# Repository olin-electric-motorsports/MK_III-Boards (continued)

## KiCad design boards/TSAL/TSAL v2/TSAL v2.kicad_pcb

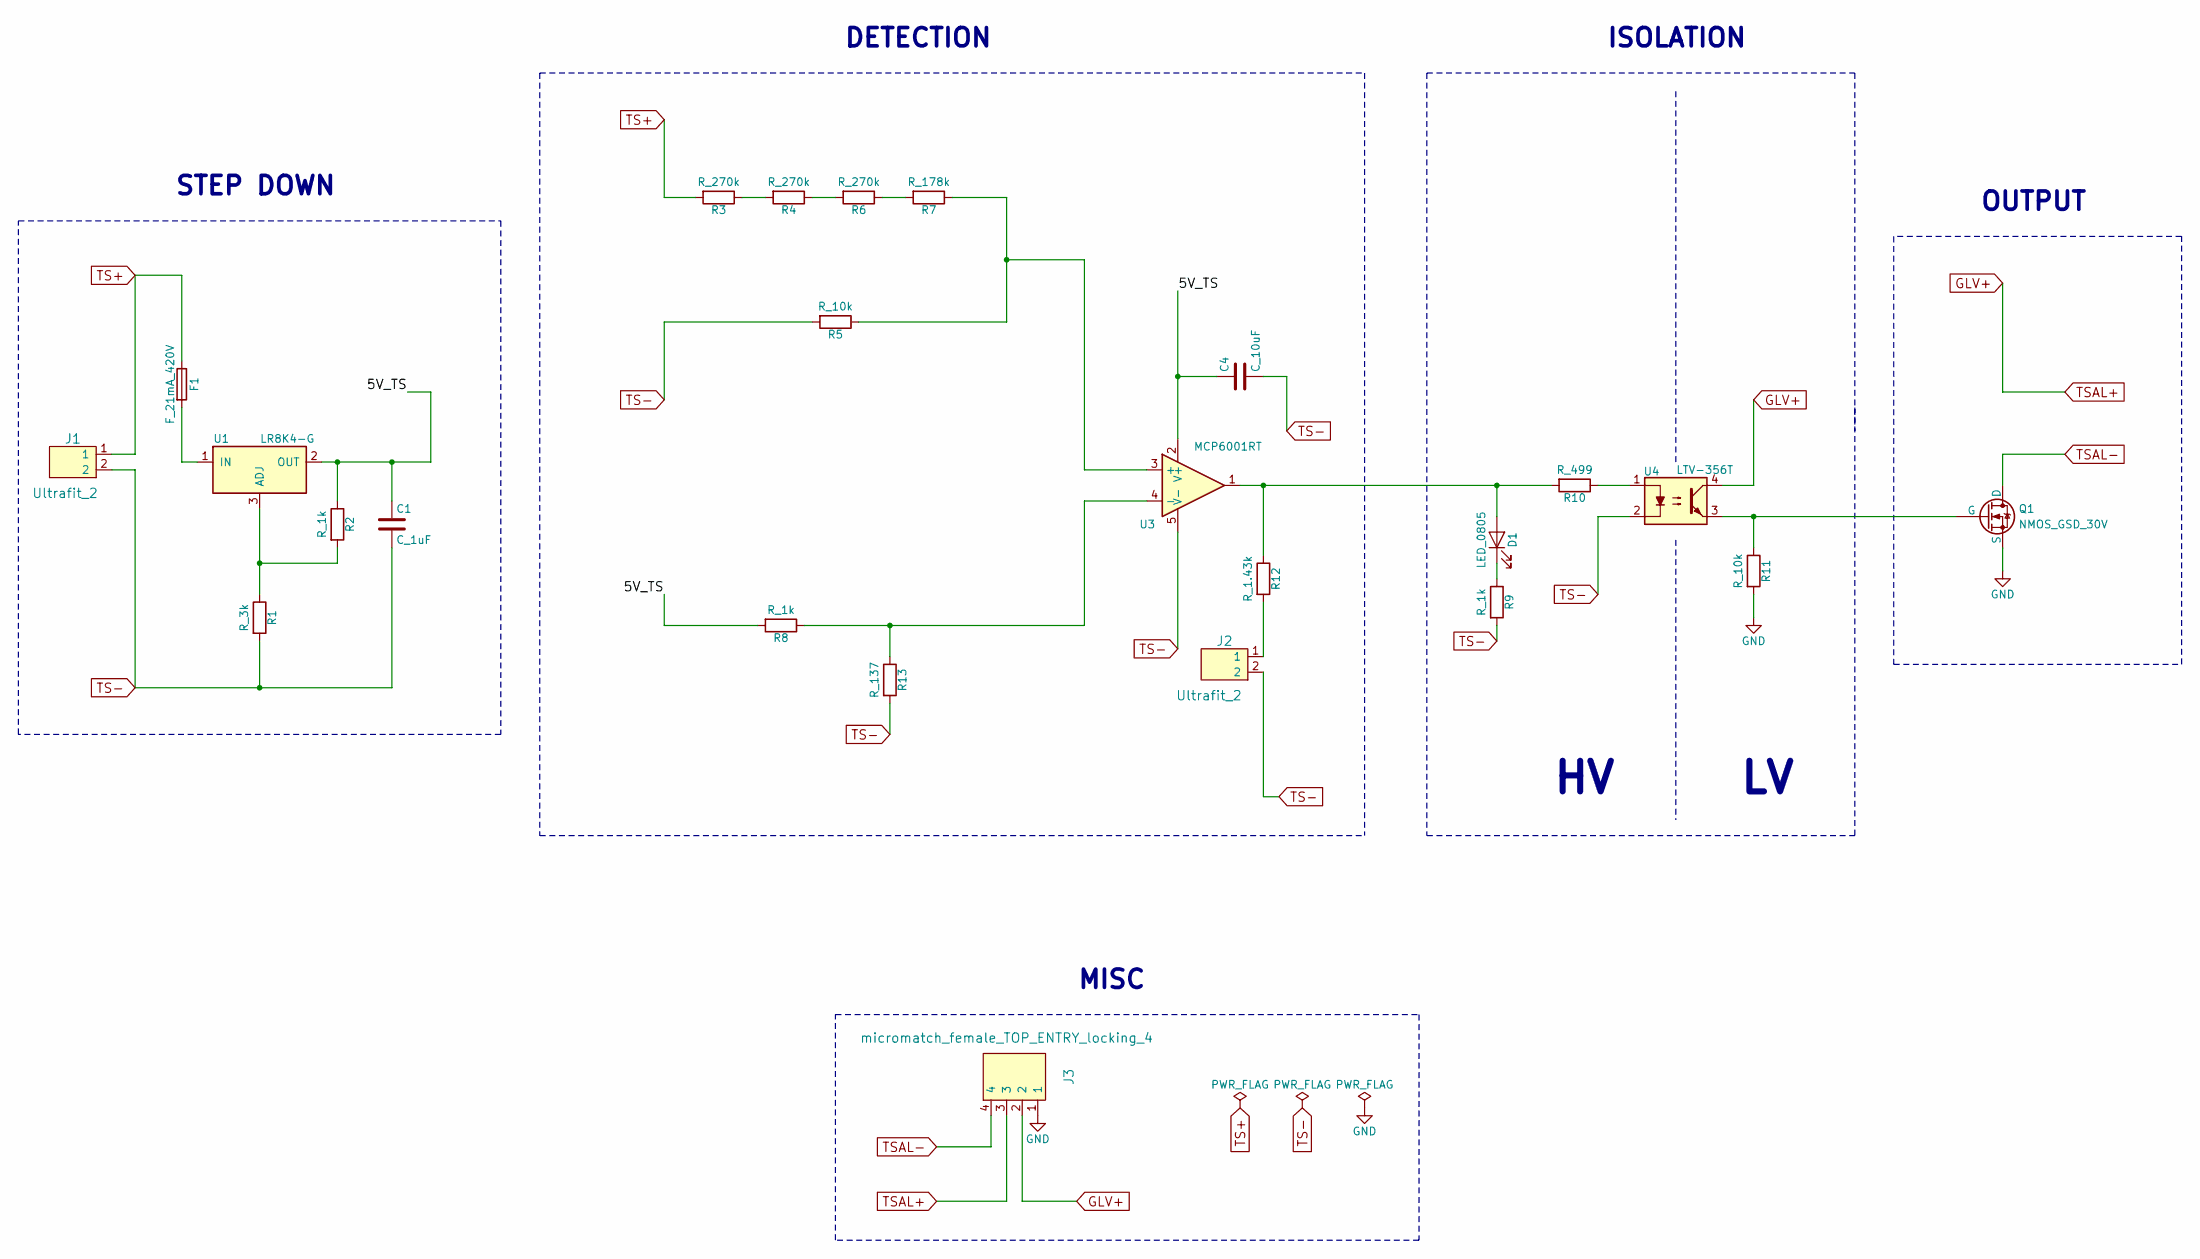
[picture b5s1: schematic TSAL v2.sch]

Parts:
C1: C_1uF; C_0805_OEM; MPN 478-10487-1-ND
C4: C_10uF; C_0805_OEM; MPN 478-5167-1-ND
D1: LED_0805; LED_0805_OEM; MPN 475-1410-1-ND
F1: F_21mA_420V; MPN 495-75309-ND
J1, J2: Ultrafit_2; MPN WM11570-ND
J3: micromatch_female_TOP_ENTRY_locking_4; micromatch_female_vert_4; MPN 338068-4
Q1: NMOS_GSD_30V; SOT-23; MPN SSM3K333RLFCT-ND
R1: R_3k; R_0805_OEM; MPN RMCF0805FT3K00CT-ND
R2, R8, R9: R_1k; R_0805_OEM; MPN RNCP0805FTD1K00CT-ND
R3, R4, R6: R_270k; R_0805_OEM; MPN P270KDACT-ND
R5, R11: R_10k; R_0805_OEM; MPN CRS0805-FX-1002ELFCT-ND
R7: R_178k; R_0805_OEM; MPN P178KDATR-ND
R10: R_499; R_0805_OEM; MPN RC0805FR-07499RL
R12: R_1.43k; R_0805_OEM; MPN A103351CT-ND
R13: R_137; R_0805_OEM; MPN A110460CT-ND
U1: LR8K4-G; TO-252-3_TabPin2; MPN 689-LR8K4-G
U3: MCP6001RT; SOT-23-5_OEM; MPN MCP6001RT-I/OTCT-ND
U4: LTV-356T; SO-4_4.4x3.6mm_Pitch2.54mm

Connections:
/5V_TS: C1.1, C4.1, R2.1, R8.2, U1.2 (OUT), U3.2 (V+)
GLV+: J3.2, J3.3, U4.4
GND: J3.1, Q1.2 (S), R11.2
unnamed: D1.1 (K), R9.1
unnamed: D1.2 (A), R10.2, R12.1, U3.1
unnamed: F1.2, U1.1 (IN)
unnamed: J2.1, R12.2
unnamed: Q1.1 (G), R11.1, U4.3
unnamed: R1.1, R2.2, U1.3 (ADJ)
unnamed: R3.1, R4.2
unnamed: R4.1, R6.2
unnamed: R5.1, R7.1, U3.3 (+)
unnamed: R6.1, R7.2
unnamed: R10.1, U4.1
unnamed: R8.1, R13.1, U3.4 (-)
TS+: F1.1, J1.1, R3.2
TS-: C1.2, C4.2, J1.2, J2.2, R1.2, R5.2, R9.2, R13.2, U3.5 (V-), U4.2
TSAL-: J3.4, Q1.3 (D)

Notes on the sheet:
STEP DOWN
DETECTION
ISOLATION
OUTPUT
MISC

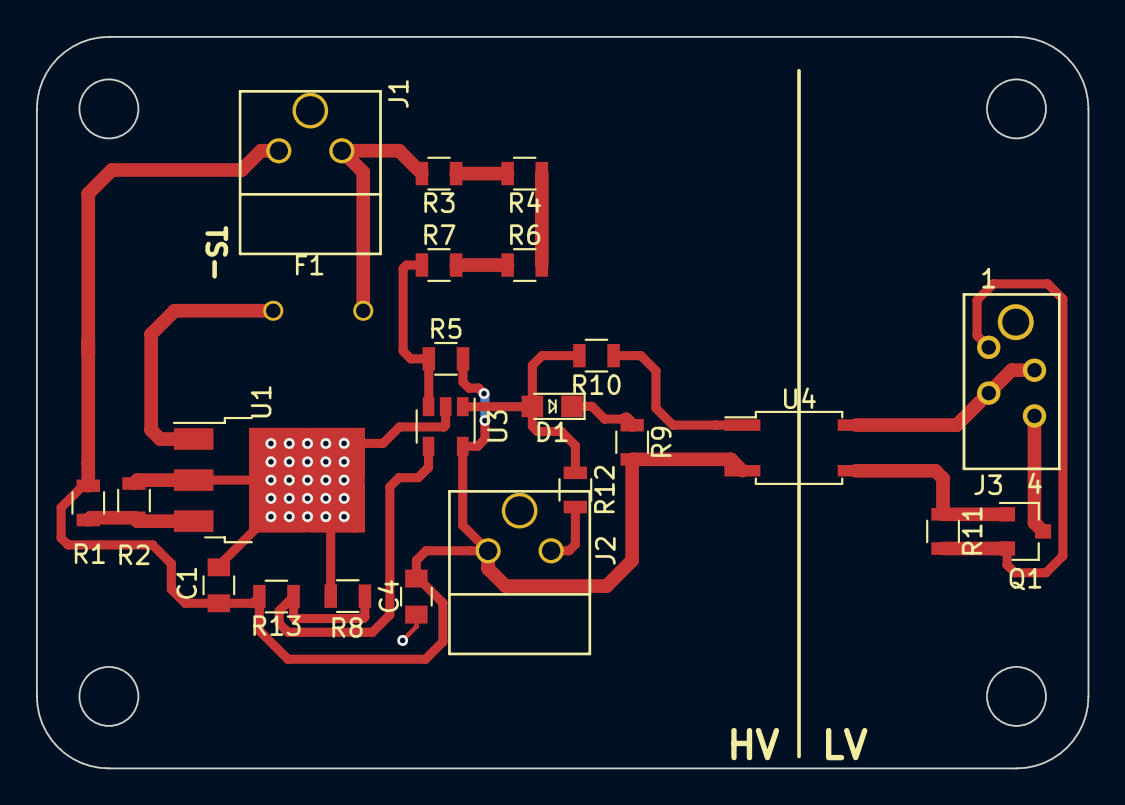
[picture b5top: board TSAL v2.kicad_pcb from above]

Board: 2 copper layers, 58.4 x 40.6 mm, 24 parts (0 on the bottom side), 18 nets.

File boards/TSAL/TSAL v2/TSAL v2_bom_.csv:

Component,Description,Part,References,Value,Footprint,Quantity Per PCB,Datasheet,Package,MPN,MFN,PurchasingLink,Webpage
1,Cap 50V 0.1uF 10% 0805,C_0.1uF,C3,C_0.1uF,C_0805_OEM,1,http://datasheets.avx.com/X7RDielectric.pdf,Value,478-3352-1-ND,Digi-Key,https://www.digikey.com/products/en?keywords=478-3352-1-ND,
2,CAP CER 10UF 10V X5R 0805,C_10uF,C4,C_10uF,C_0805_OEM,1,http://datasheets.avx.com/cx5r.pdf,Value,478-5167-1-ND,Digi-Key,https://www.digikey.com/product-detail/en/avx-corporation/08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,
3,CAP CER 1UF 25V X7R 0805,C_1uF,C1 C2,C_1uF,C_0805_OEM,2,http://datasheets.avx.com/X7RDielectric.pdf,Value,478-10487-1-ND,Digi-Key,https://www.digikey.com/product-detail/en/avx-corporation/08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,
4,LED_0805,LED_0805,D1,LED_0805,LED_0805_OEM,1,http://www.osram-os.com/Graphics/XPic9/00078860_0.pdf,Value,475-1410-1-ND,Digi-Key,https://www.digikey.com/products/en?keywords=475-1410-1-ND,
5,PTC Fuse 420V 21mA,F_21mA_420V,F1,F_21mA_420V,F_21mA_420V,1,https://en.tdk.eu/inf/55/db/PTC/PTC_OC_Leaded_380V_500V.pdf,,495-75309-ND,Digi-Key,https://www.digikey.com/product-detail/en/epcos-tdk/B59884C0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,
6,ULTRAFIT CONN HDR 02CKT,Ultrafit_2,J1 J2,Ultrafit_2,Ultrafit_2,2,,Value,WM11570-ND,Digi-Key,https://www.digikey.com/product-detail/en/molex-llc/17228611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,
7,CONN FMALE-ON-BRD 4POS VERT T/H,micromatch_female_TOP_ENTRY_locking_4,J3,micromatch_female_TOP_ENTRY_locking_4,micromatch_female_vert_4,1,http://www.te.com/commerce/DocumentDelivery/DDEController?Ac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,Value,338068-4,Digi-Key,https://www.digikey.com/product-detail/en/te-connectivity-am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,
8,N-channel MOSFET,NMOS_GSD_30V,Q1,NMOS_GSD_30V,SOT-23,1,https://www.digikey.com/products/en?keywords=SSM3K333RLFCT-ND,Value,SSM3K333RLFCT-ND,Digi-Key,https://www.digikey.com/products/en?keywords=SSM3K333RLFCT-ND,
9,RES SMD 1.43KOHM 0.1% 1/10W 0805,R_1.43k,R12,R_1.43k,R_0805_OEM,1,https://media.digikey.com/pdf/Data%20Sheets/Tyco%20Electonic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,,A103351CT-ND,Digi-Key,https://www.digikey.com/product-detail/en/te-connectivity-pa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,
10,Res 10k 1%,R_10k,R5 R11,R_10k,R_0805_OEM,2,http://www.bourns.com/data/global/pdfs/CRS.pdf,Value,CRS0805-FX-1002ELFCT-ND,Digi-Key,https://www.digikey.com/products/en?keywords=CRS0805-FX-1002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,
11,RES SMD 178K OHM 0.1% 1/8W 0805,R_178k,R7,R_178k,R_0805_OEM,1,https://industrial.panasonic.com/cdbs/www-data/pdf/RDM0000/A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,,P178KDATR-ND,Digikey,,https://www.digikey.com/product-detail/en/panasonic-electron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
12,Res 1k 1%,R_1k,R2 R8 R9,R_1k,R_0805_OEM,3,https://www.seielect.com/Catalog/SEI-rncp.pdf,Value,RNCP0805FTD1K00CT-ND,Digi-Key,https://www.digikey.com/products/en?keywords=RNCP0805FTD1K00CT-ND,
13,RES SMD 270K OHM 0.1% 1/8W 0805,R_270k,R3 R4 R6,R_270k,R_0805_OEM,3,https://industrial.panasonic.com/cdbs/www-data/pdf/RDM0000/A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,,P270KDACT-ND,DigiKey,,https://www.digikey.com/product-detail/en/panasonic-electron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
14,Res 3k 1% 0805 1/8W,R_3k,R1,R_3k,R_0805_OEM,1,https://www.seielect.com/Catalog/SEI-RMCF_RMCP.pdf,Value,RMCF0805FT3K00CT-ND,Digi-Key,https://www.digikey.com/product-detail/en/stackpole-electron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,
15,Res 499 1%,R_499,R10,R_499,R_0805_OEM,1,http://www.yageo.com.tw/exep/pages/download/literatures/PYu-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,Value,RC0805FR-07499RL,Digi-Key,https://www.digikey.com/product-detail/en/yageo/RC0805FR-074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,
16,Linear Voltage Regulators 450V Adj 3 Termnl,LR8K4-G,U1,LR8K4-G,TO-252-3_TabPin2,1,http://ww1.microchip.com/downloads/en/DeviceDoc/20005399B.pdf,,689-LR8K4-G,Mouser,,https://www.mouser.com/productdetail/?qs=jWmFlM7coATgElKtQd9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
17,"DC Optocoupler, Vce 80V, CTR 50%, SO-4",LTV-356T,U4,LTV-356T,SO-4_4.4x3.6mm_Pitch2.54mm,1,http://optoelectronics.liteon.com/upload/download/DS70-2001-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,,,,,
18,IC OPAMP GP 1MHZ RRO SOT23-5  1.8-6V,MCP6001RT,U3,MCP6001RT,SOT-23-5_OEM,1,http://ww1.microchip.com/downloads/en/DeviceDoc/21733j.pdf,Value,MCP6001RT-I/OTCT-ND,Digi-Key,https://www.digikey.com/product-detail/en/microchip-technolo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,
19,IC VREF SHUNT ADJ SOT353,ZXRE160,U2,ZXRE160,ZXRE160,1,https://www.diodes.com/assets/Datasheets/ZXRE160.pdf,,ZXRE160FT4-7DICT-ND,DigiKey,,https://www.digikey.com/product-detail/en/diodes-incorporate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





Component Groups:,19
Component Count:,26
Fitted Components:,26
Number of PCBs:,1
Total components:,26
Schematic Version:,
Schematic Date:,
BoM Date:,2/7/2018 4:59:53 PM
Schematic Source:,C:\Users\ugupta\Documents\GitHub\MK_III-Boards\boards\TSAL\TSAL v2\TSAL v2.sch
KiCad Version:,Eeschema 4.0.7

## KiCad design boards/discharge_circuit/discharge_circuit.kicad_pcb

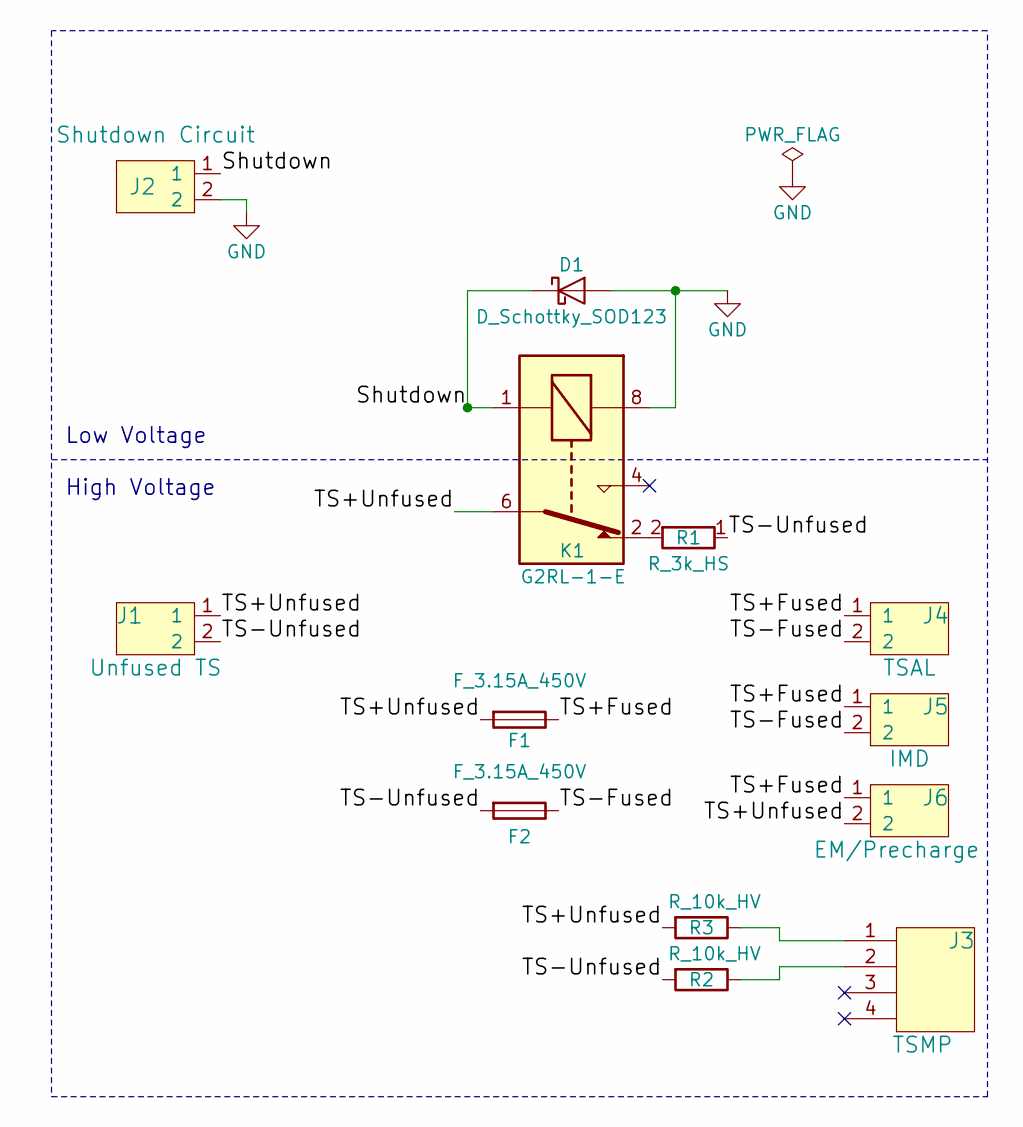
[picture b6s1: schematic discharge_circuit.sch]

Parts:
D1: D_Schottky_SOD123; D_SOD-123W_OEM; MPN 1727-2394-1-ND
F1, F2: F_3.15A_450V; Fuse_TE7_Littelfuse-807Series; MPN 80713150440
J1: Unfused TS; Ultrafit_2; MPN WM11570-ND
J2: Shutdown Circuit; Ultrafit_2; MPN WM11570-ND
J3: TSMP; mx150l_2
J4: TSAL; Ultrafit_2; MPN WM11570-ND
J5: IMD; Ultrafit_2; MPN WM11570-ND
J6: EM/Precharge; Ultrafit_2; MPN WM11570-ND
K1: G2RL-1-E; Relay_SPDT_OMRON-G2RL-1-E; MPN Z2834-ND
R1: R_3k_HS; R_3k_HS_TO247; MPN AP101 3K J
R2, R3: R_10k_HV; R_10K_HV; MPN PPC5D10.0KCT-ND

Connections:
/Shutdown: D1.1 (K), J2.1, K1.1
/TS+Fused: F1.1, J4.1, J5.1, J6.1
/TS+Unfused: F1.2, J1.1, J6.2, K1.6, R3.2
/TS-Fused: F2.1, J4.2, J5.2
/TS-Unfused: F2.2, J1.2, R1.1, R2.2
GND: D1.2 (A), J2.2, K1.8
unnamed: J3.1, R3.1
unnamed: J3.2, R2.1
unnamed: K1.2, R1.2

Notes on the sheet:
High Voltage
Low Voltage

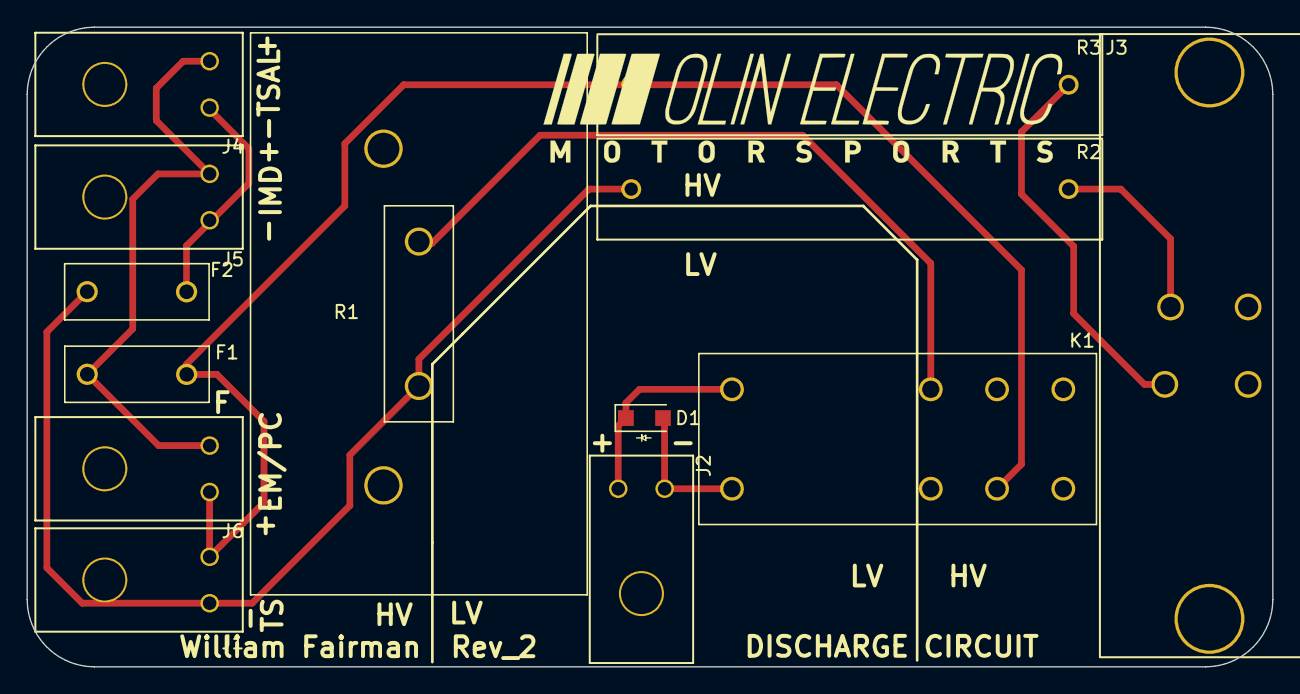
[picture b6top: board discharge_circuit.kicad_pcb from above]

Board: 2 copper layers, 94.0 x 48.3 mm, 13 parts (0 on the bottom side), 9 nets.

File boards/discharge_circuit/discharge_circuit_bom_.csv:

Component,Description,Part,References,Value,Footprint,Quantity Per PCB,Datasheet,MPN,MFN,PurchasingLink,Package
1,DIODE SCHOTTKY 100V 1A SOD123,D_Schottky_SOD123,D1,D_Schottky_SOD123,D_SOD-123W_OEM,1,https://assets.nexperia.com/documents/data-sheet/PMEG10010ELR.pdf,1727-2394-1-ND,Digi-Key,https://www.digikey.com/product-detail/en/nexperia-usa-inc/P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,
2,,F_3.15A_450V,F1 F2,F_3.15A_450V,Fuse_TE7_Littelfuse-807Series,2,http://www.mouser.com/ds/2/240/Littelfuse_Fuse_807_Datasheet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,80713150440,Mouser,https://www.mouser.com/ProductDetail/Littelfuse/80713150440/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,Value
3,ULTRAFIT CONN HDR 02CKT,Ultrafit_2,J6,EM/Precharge,Ultrafit_2,1,,WM11570-ND,Digi-Key,https://www.digikey.com/product-detail/en/molex-llc/17228611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,Value
4,ULTRAFIT CONN HDR 02CKT,Ultrafit_2,J5,IMD,Ultrafit_2,1,,WM11570-ND,Digi-Key,https://www.digikey.com/product-detail/en/molex-llc/17228611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,Value
5,ULTRAFIT CONN HDR 02CKT,Ultrafit_2,J2,Shutdown Circuit,Ultrafit_2,1,,WM11570-ND,Digi-Key,https://www.digikey.com/product-detail/en/molex-llc/17228611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,Value
6,ULTRAFIT CONN HDR 02CKT,Ultrafit_2,J4,TSAL,Ultrafit_2,1,,WM11570-ND,Digi-Key,https://www.digikey.com/product-detail/en/molex-llc/17228611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,Value
7,mx150L_2,mx150L_2,J3,TSMP,mx150l_2,1,http://www.literature.molex.com/SQLImages/kelmscott/Molex/PD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,,,,Value
8,ULTRAFIT CONN HDR 02CKT,Ultrafit_2,J1,Unfused TS,Ultrafit_2,1,,WM11570-ND,Digi-Key,https://www.digikey.com/product-detail/en/molex-llc/17228611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,Value
9,"Omron G5G relay, Miniature Single Pole, SPDT, 10A",G2RL-1-E,K1,G2RL-1-E,Relay_SPDT_OMRON-G2RL-1-E,1,http://omronfs.omron.com/en_US/ecb/products/pdf/en-g2rl.pdf,Z2834-ND,Digi-Key,https://www.digikey.com/product-detail/en/omron-electronics-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,Value
10,Res 10k 1%,R_10k_HV,R2 R3,R_10k_HV,R_10K_HV,2,http://www.vishay.com/docs/28731/pacserie.pdf,PPC5D10.0KCT-ND,Digi-Key,https://www.digikey.com/products/en?keywords=PPC5D10.0KCT-ND,Value
11,3k ohm 100 w rating,R_3k_HS,R1,R_3k_HS,R_3k_HS_TO247,1,http://dpk3n3gg92jwt.cloudfront.net/domains/ohmite/pdf/acl_a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,AP101 3K J,Digi-Key,https://www.digikey.com/product-detail/en/ohmite/AP101-3K-J/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,Value





Component Groups:,11
Component Count:,13
Fitted Components:,13
Number of PCBs:,1
Total components:,13
Schematic Version:,
Schematic Date:,
BoM Date:,Mon 05 Feb 2018 09:41:58 PM EST
Schematic Source:,/home/william/Desktop/Formula/MK_III-Boards/boards/discharge_circuit/discharge_circuit.sch
KiCad Version:,Eeschema 4.0.7-e2-6376~58~ubuntu16.04.1

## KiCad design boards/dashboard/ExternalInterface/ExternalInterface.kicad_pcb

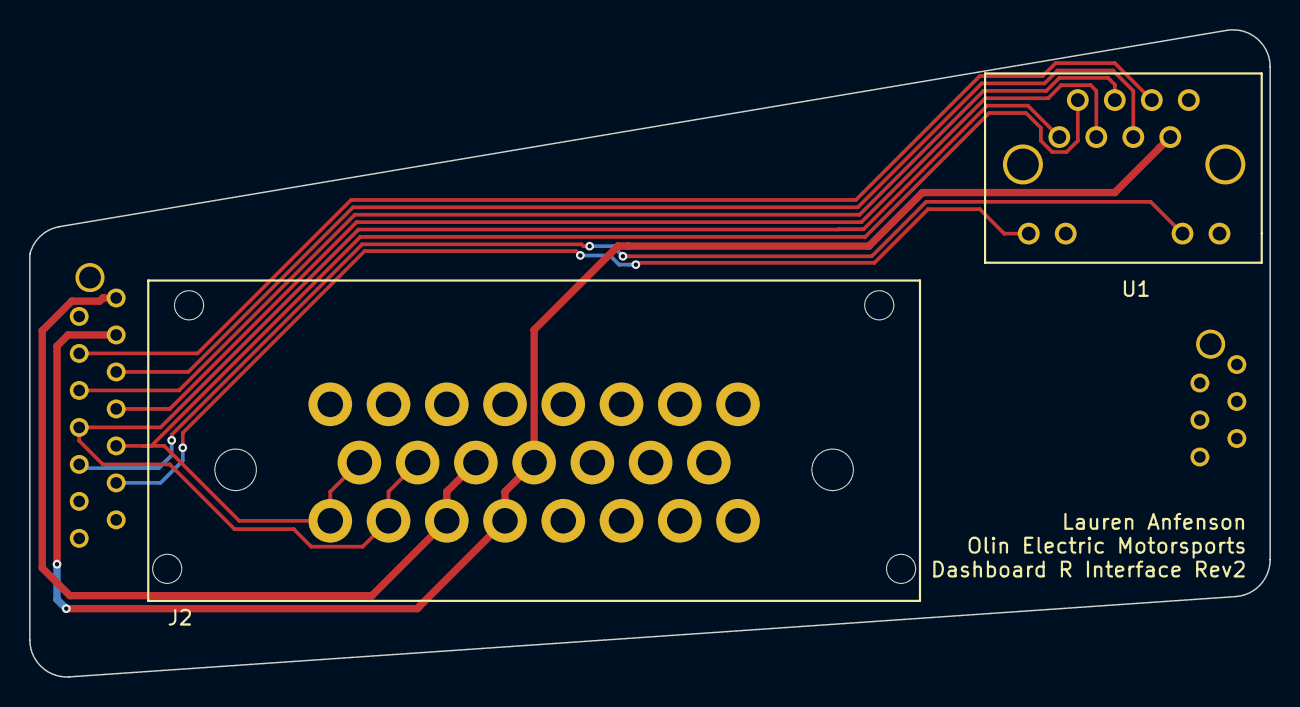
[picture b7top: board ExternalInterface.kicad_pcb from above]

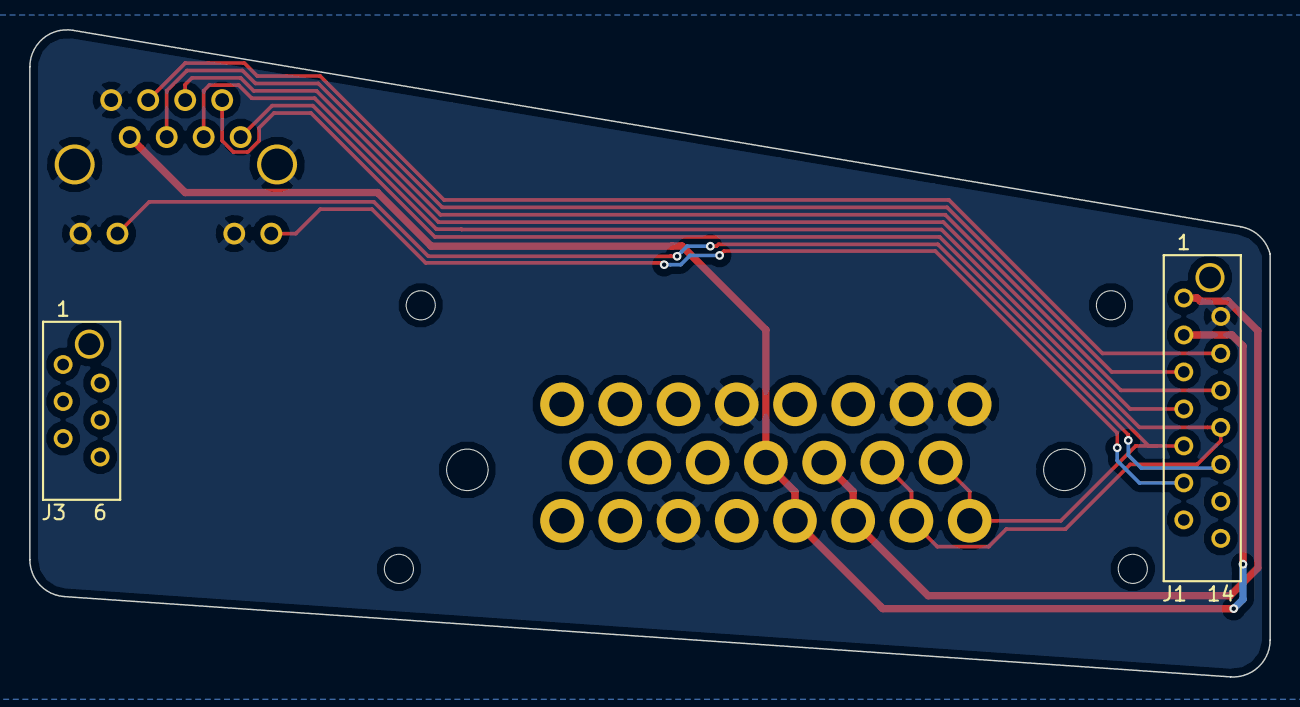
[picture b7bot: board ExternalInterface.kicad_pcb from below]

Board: 2 copper layers, 85.2 x 44.4 mm, 4 parts (2 on the bottom side), 11 nets.

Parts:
J1: micromatch_female_TOP_ENTRY_locking_14; micromatch_female_vert_14
J2: Ampseal_23
J3: micromatch_female_TOP_ENTRY_locking_6; micromatch_female_vert_6
U1: RJ45_VT; RJ45-Vertical

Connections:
+12V: J1.1, J2.11, J2.18
AT_RESET: J1.7, U1.3
CANH: J1.9, J2.9, J2.16, U1.2
CANL: J1.8, J2.10, J2.17, U1.1
GND: J1.2, J2.1, J2.2, J2.5, J2.21, U1.8, U1.9, U1.11, U1.13, U1.14
LED1: J1.10, U1.10
LED2: J1.11, U1.12
MISO: J1.5, U1.5
MOSI: J1.4, U1.6
SCK: J1.6, U1.4
VCC: J1.3, J2.12, J2.19, U1.7

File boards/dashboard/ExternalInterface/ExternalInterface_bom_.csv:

Component,Description,Part,References,Value,Footprint,Quantity Per PCB,Datasheet,Package,MPN,MFN,PurchasingLink
1,Waterproof Panel-Mount Connector RA 14-Pin,Ampseal_14,J2,Ampseal_14,Ampseal_14,1,,,,,
2,CONN FMALE-ON-BRD 14POS VERT T/H,micromatch_female_TOP_ENTRY_locking_14,J1,micromatch_female_TOP_ENTRY_locking_14,micromatch_female_vert_14,1,,Value,A99502CT-ND,Digi-Key,https://www.digikey.com/product-detail/en/te-connectivity-am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
3,CONN FMALE-ON-BRD 6POS VERT T/H,micromatch_female_TOP_ENTRY_locking_6,J3,micromatch_female_TOP_ENTRY_locking_6,micromatch_female_vert_6,1,,Value,A99437CT-ND,Digi-Key,https://www.digikey.com/product-detail/en/te-connectivity-am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
4,,RJ45_VT,U1,RJ45_VT,RJ45-Vertical,1,,,,,





Component Groups:,4
Component Count:,4
Fitted Components:,4
Number of PCBs:,1
Total components:,4
Schematic Version:,
Schematic Date:,
BoM Date:,Wed 21 Feb 2018 10:11:25 PM EST
Schematic Source:,/home/lanfenson/MK_III-Boards-master/boards/dashboard/ExternalInterface/ExternalInterface.sch
KiCad Version:,Eeschema 4.0.7-e2-6376~58~ubuntu16.04.1

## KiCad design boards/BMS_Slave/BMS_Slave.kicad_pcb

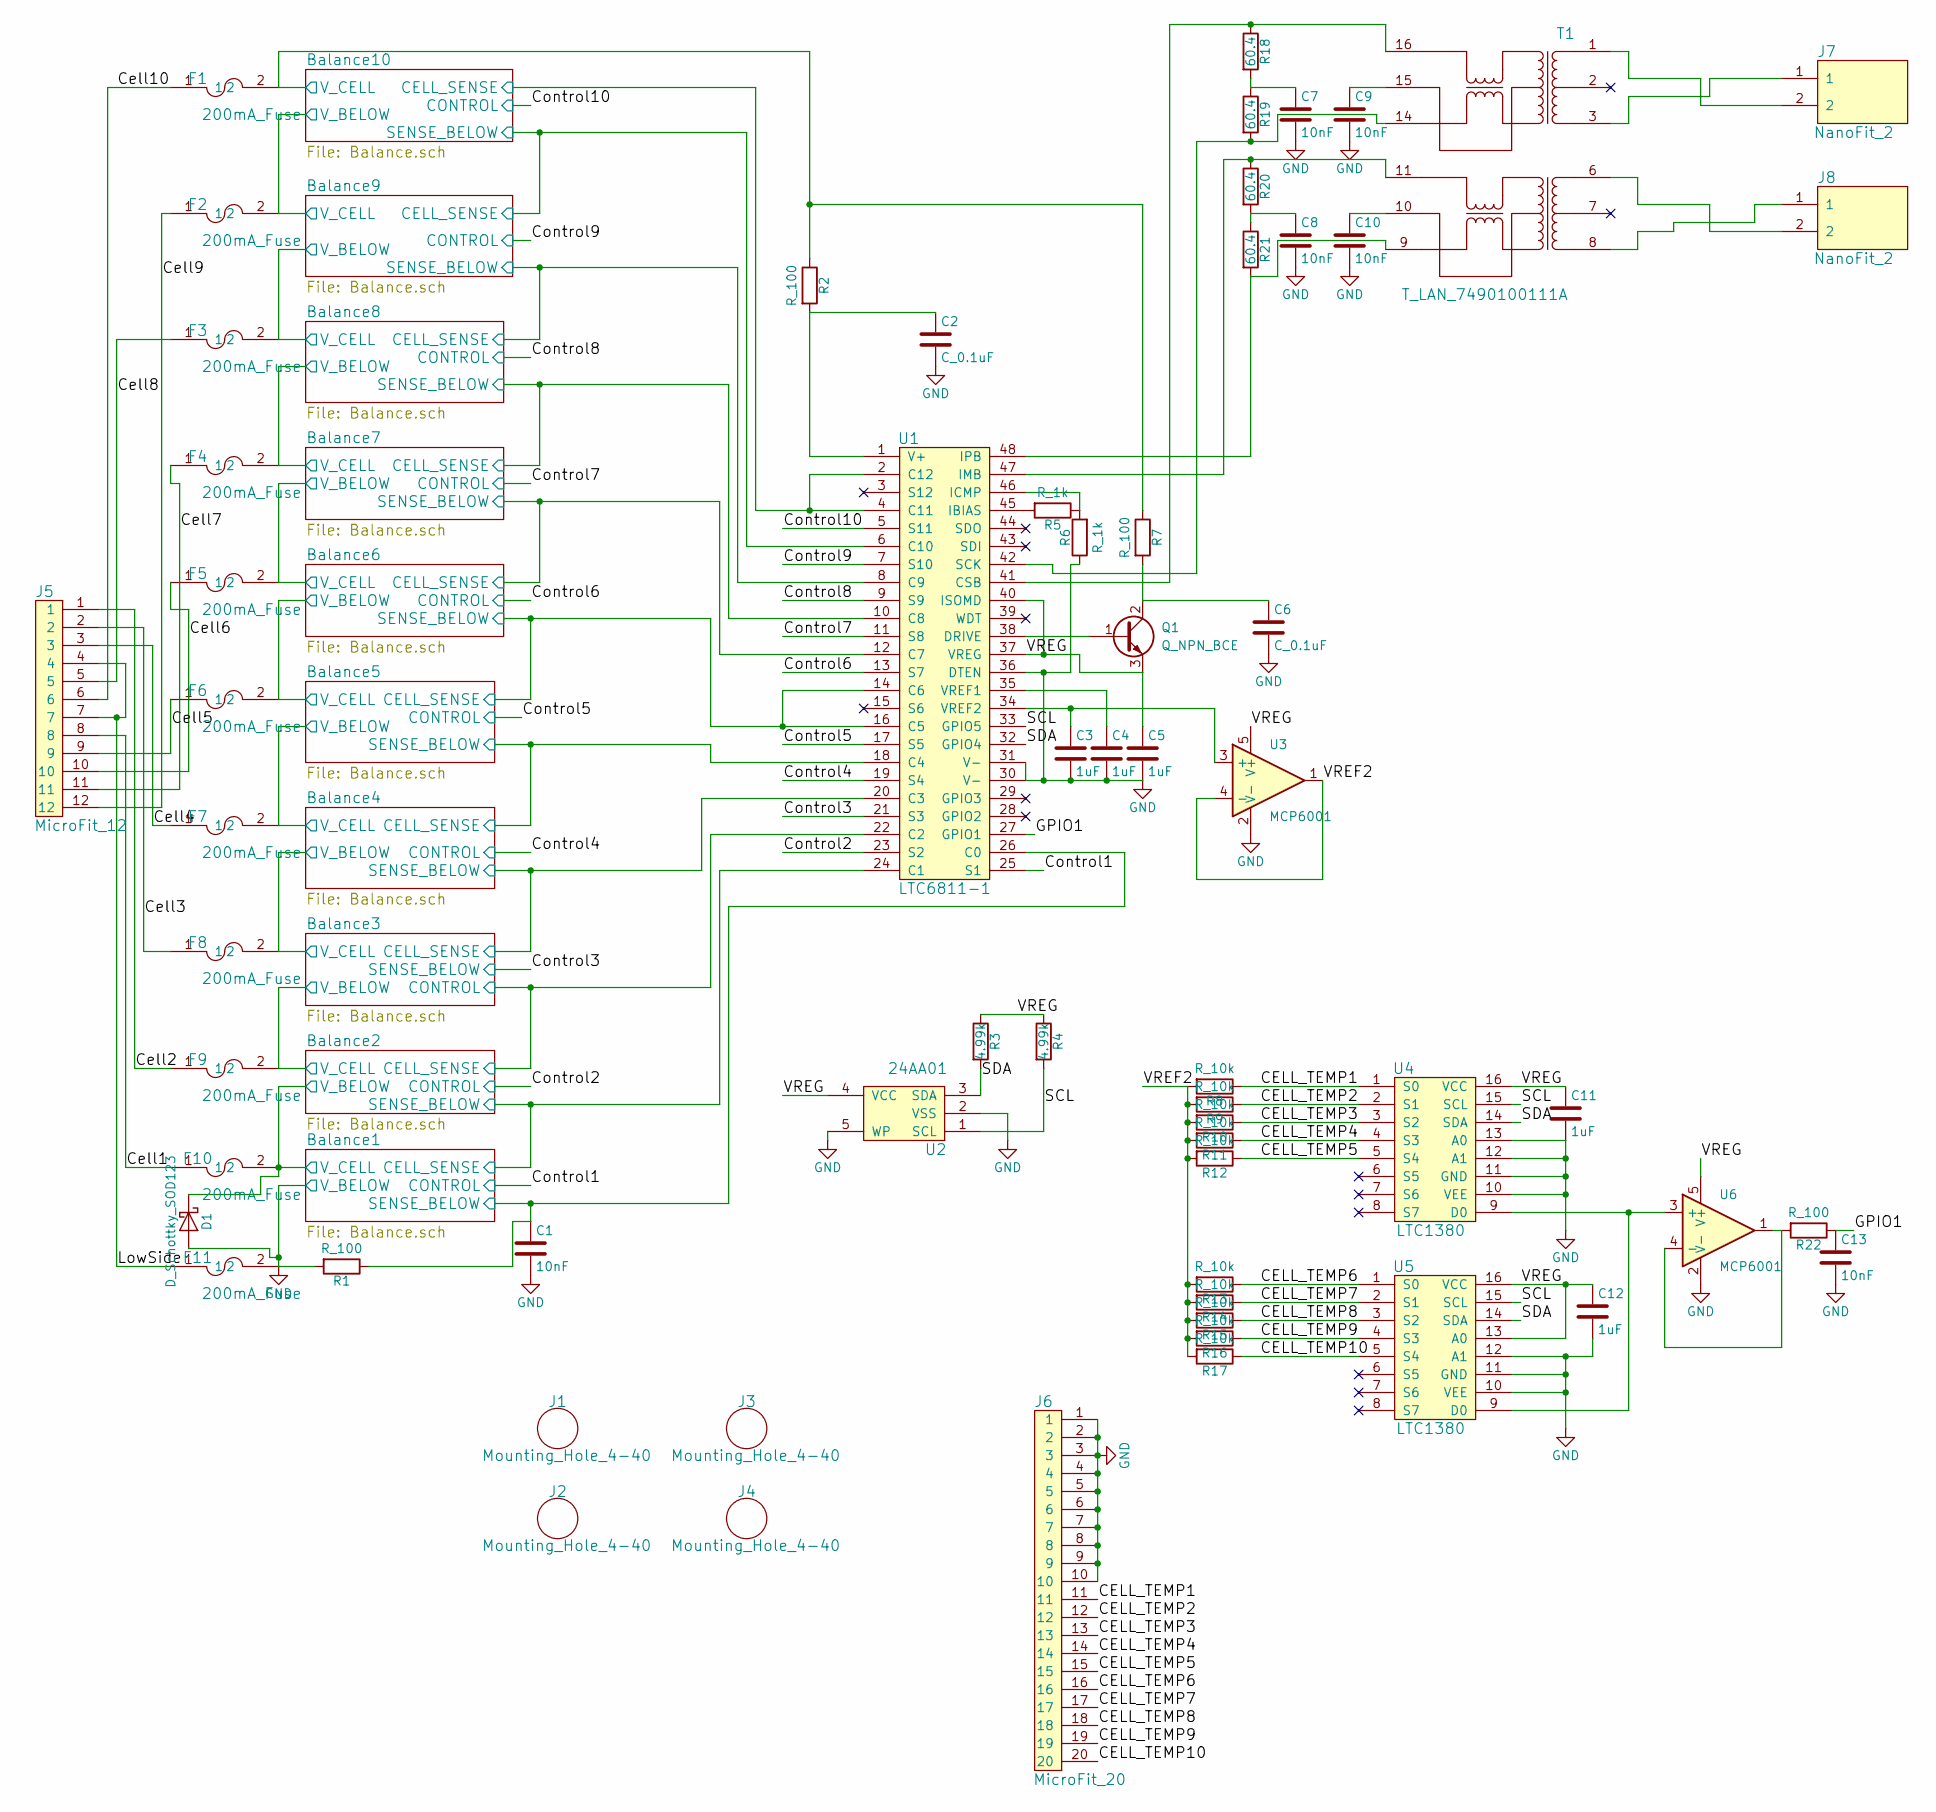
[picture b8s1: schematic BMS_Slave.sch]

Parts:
C1, C7, C8, C9, C10, C13: 10nF; C_0805_OEM
C2, C6: C_0.1uF; C_0805_OEM; MPN 478-3352-1-ND
C3, C4, C5, C11, C12: 1uF; C_0805_OEM
D1: D_Schottky_SOD123; D_SOD-123W_OEM; MPN 1727-2394-1-ND
F1, F2, F3, F4, F5, F6, F7, F8, F9, F10, F11: 200mA_Fuse; Fuse_1812
J1, J3: Mounting_Hole_4-40; MPN Value
J2, J4: Mounting_Hole_4-40; Mounting_Hole_Insert_4-40; MPN Value
J5: MicroFit_12; Microfit3_Header_02x06_Angled_OEM
J6: MicroFit_20; Molex_Microfit3_Header_02x10_Angled_OEM
J7, J8: NanoFit_2; Molex_NanoFit_1x02x2.50mm_Angled_OEM
Q1: Q_NPN_BCE; SOT-223
R1, R2, R7, R22: R_100; R_0805_OEM; MPN RNCP0805FTD100RCT-ND
R3, R4: 4.99k; R_0805_OEM
R5, R6: R_1k; R_0805_OEM; MPN RNCP0805FTD1K00CT-ND
R8, R9, R10, R11, R12, R13, R14, R15, R16, R17: R_10k; R_0805_OEM; MPN CRS0805-FX-1002ELFCT-ND
R18, R19, R20, R21: 60.4; R_0805_OEM
T1: T_LAN_7490100111A; 7490100111A
U1: LTC6811-1; TSSOP-48_LTC6811-1
U2: 24AA01; SOT-23-5_OEM
U3, U6: MCP6001; SOT-23-5_OEM
U4, U5: LTC1380; SSOP-16_LTC1380

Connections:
/Balance1/CELL_SENSE: U1.24 (C1); also elsewhere on the board
/Balance1/SENSE_BELOW: C1.1, R1.1, U1.26 (C0); also elsewhere on the board
/Balance2/CELL_SENSE: U1.22 (C2); also elsewhere on the board
/Balance2/V_BELOW: D1.1 (K), F10.2; also elsewhere on the board
/Balance3/CELL_SENSE: U1.20 (C3); also elsewhere on the board
/Balance3/V_BELOW: F9.2; also elsewhere on the board
/Balance4/CELL_SENSE: U1.18 (C4); also elsewhere on the board
/Balance4/V_BELOW: F8.2; also elsewhere on the board
/Balance5/CELL_SENSE: U1.14 (C6), U1.16 (C5); also elsewhere on the board
/Balance5/V_BELOW: F7.2; also elsewhere on the board
/Balance6/CELL_SENSE: U1.12 (C7); also elsewhere on the board
/Balance6/V_BELOW: F6.2; also elsewhere on the board
/Balance7/CELL_SENSE: U1.10 (C8); also elsewhere on the board
/Balance8/CELL_SENSE: U1.8 (C9); also elsewhere on the board
/Balance8/V_BELOW: F4.2; also elsewhere on the board
/Balance9/CELL_SENSE: U1.6 (C10); also elsewhere on the board
/Balance10/CELL_SENSE: U1.2 (C12), U1.4 (C11); also elsewhere on the board
/Balance10/V_BELOW: F2.2; also elsewhere on the board
/Balance10/V_CELL: F1.2, R2.1, R7.1; also elsewhere on the board
/CELL_TEMP1: J6.11, R8.1, U4.1 (S0)
/CELL_TEMP2: J6.12, R9.1, U4.2 (S1)
/CELL_TEMP3: J6.13, R10.1, U4.3 (S2)
/CELL_TEMP4: J6.14, R11.1, U4.4 (S3)
/CELL_TEMP5: J6.15, R12.1, U4.5 (S4)
/CELL_TEMP6: J6.16, R13.1, U5.1 (S0)
/CELL_TEMP7: J6.17, R14.1, U5.2 (S1)
/CELL_TEMP8: J6.18, R15.1, U5.3 (S2)
/CELL_TEMP9: J6.19, R16.1, U5.4 (S3)
/CELL_TEMP10: J6.20, R17.1, U5.5 (S4)
/Cell1: F10.1, J5.8
/Cell2: F9.1, J5.1
/Cell3: F8.1, J5.2
/Cell4: F7.1, J5.3
/Cell5: F6.1, J5.9
/Cell6: F5.1, J5.10
/Cell7: F4.1, J5.11
/Cell8: F3.1, J5.5
/Cell9: F2.1, J5.12
/Cell10: F1.1, J5.6
/Control1: U1.25 (S1); also elsewhere on the board
/Control2: U1.23 (S2); also elsewhere on the board
/Control3: U1.21 (S3); also elsewhere on the board
/Control4: U1.19 (S4); also elsewhere on the board
/Control5: U1.17 (S5); also elsewhere on the board
/Control6: U1.13 (S7); also elsewhere on the board
/Control7: U1.11 (S8); also elsewhere on the board
/Control8: U1.9 (S9); also elsewhere on the board
/Control9: U1.7 (S10); also elsewhere on the board
/Control10: U1.5 (S11); also elsewhere on the board
/GPIO1: C13.1, R22.1, U1.27 (GPIO1)
/LowSide: F11.1, J5.4, J5.7
/SCL: R4.2, U1.33 (GPIO5), U2.1 (SCL), U4.15 (SCL), U5.15 (SCL)
/SDA: R3.2, U1.32 (GPIO4), U2.3 (SDA), U4.14 (SDA), U5.14 (SDA)
/VREF2: R8.2, R9.2, R10.2, R11.2, R12.2, R13.2, R14.2, R15.2, R16.2, R17.2, U3.1, U3.4 (-)
/VREG: C5.1, C11.1, C12.1, Q1.3 (E), R3.1, R4.1, U1.37 (VREG), U1.40 (ISOMD), U2.4 (VCC), U3.5 (V+), U4.16 (VCC), U5.13 (A0), U5.16 (VCC), U6.5 (V+)
GND: C1.2, C2.2, C3.2, C4.2, C5.2, C6.2, C7.2, C8.2, C9.2, C10.2, C11.2, C12.2, C13.2, D1.2 (A), F11.2, J6.1, J6.2, J6.3, J6.4, J6.5, J6.6, J6.7, J6.8, J6.9, J6.10, R1.2, R6.1, U1.30 (V-), U1.31 (V-), U1.36 (DTEN), U2.2 (VSS), U2.5 (WP), U3.2 (V-), U4.10 (VEE), U4.11 (GND), U4.12 (A1), U4.13 (A0), U5.10 (VEE), U5.11 (GND), U5.12 (A1), U6.2 (V-); also elsewhere on the board
unnamed: C2.1, R2.2, U1.1 (V+)
unnamed: C3.1, U1.34 (VREF2), U3.3 (+)
unnamed: C4.1, U1.35 (VREF1)
unnamed: C6.1, Q1.2 (C), R7.2
unnamed: C7.1, R18.2, R19.1
unnamed: C8.1, R20.2, R21.1
unnamed: C9.1, T1.15
unnamed: C10.1, T1.10
unnamed: J7.1, T1.3
unnamed: J7.2, T1.1
unnamed: J8.1, T1.8
unnamed: J8.2, T1.6
unnamed: Q1.1 (B), U1.38 (DRIVE)
unnamed: R5.1, R6.2, U1.46 (ICMP)
unnamed: R5.2, U1.45 (IBIAS)
unnamed: R18.1, T1.16, U1.41 (CSB)
unnamed: R19.2, T1.14, U1.42 (SCK)
unnamed: R20.1, T1.11, U1.47 (IMB)
unnamed: R21.2, T1.9, U1.48 (IPB)
unnamed: R22.2, U6.1, U6.4 (-)
unnamed: U4.9 (D0), U5.9 (D0), U6.3 (+)

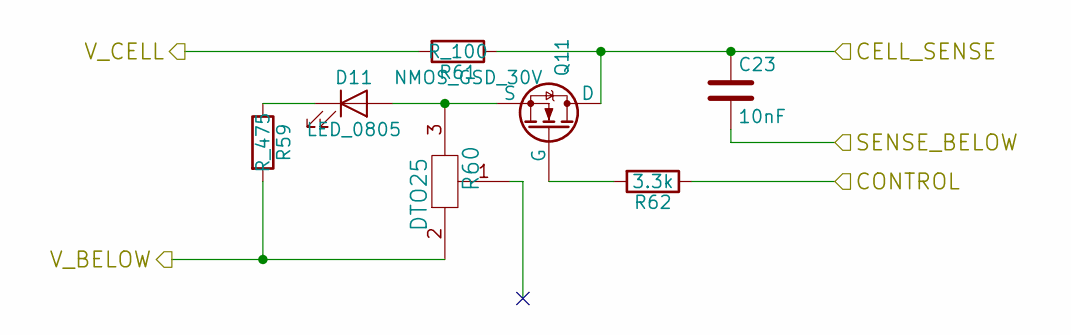
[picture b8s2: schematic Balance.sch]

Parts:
C14: 10nF; C_0805_OEM
D2: LED_0805; LED_0805_OEM; MPN 475-1410-1-ND
Q2: NMOS_GSD_30V; SOT-23F; MPN SSM3K333RLFCT-ND
R23: R_475; R_0805_OEM; MPN 311-475CRCT-ND
R25: R_100; R_0805_OEM; MPN RNCP0805FTD100RCT-ND
R26: 3.3k; R_0805_OEM
R32: DTO25

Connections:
/Balance8/CELL_SENSE: C14.2; also elsewhere on the board
/Balance9/CELL_SENSE: C14.1, Q2.3 (D), R25.1; also elsewhere on the board
/Balance10/V_BELOW: R25.2; also elsewhere on the board
/Control9: R26.1; also elsewhere on the board
unnamed: D2.1 (K), R23.1
unnamed: Q2.1 (G), R26.2

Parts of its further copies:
C15, C16, C17, C18, C19, C20, C21, C22, C23: 10nF; C_0805_OEM
D3, D4, D5, D6, D7, D8, D9, D10, D11: LED_0805; LED_0805_OEM; MPN 475-1410-1-ND
Q3, Q4, Q5, Q6, Q7, Q8, Q9, Q10, Q11: NMOS_GSD_30V; SOT-23F; MPN SSM3K333RLFCT-ND
R24, R28, R36, R40, R44, R48, R52, R56, R60: DTO25
R27, R31, R35, R39, R43, R47, R51, R55, R59: R_475; R_0805_OEM; MPN 311-475CRCT-ND
R29, R33, R37, R41, R45, R49, R53, R57, R61: R_100; R_0805_OEM; MPN RNCP0805FTD100RCT-ND
R30, R34, R38, R42, R46, R50, R54, R58, R62: 3.3k; R_0805_OEM

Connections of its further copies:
/Balance1/CELL_SENSE: C21.2, C22.1, Q10.3 (D), R57.1; also elsewhere on the board
/Balance1/SENSE_BELOW: C22.2; also elsewhere on the board
/Balance2/CELL_SENSE: C21.1, Q9.3 (D), R50.1, R53.1; also elsewhere on the board
/Balance2/V_BELOW: R51.2, R52.2, R57.2; also elsewhere on the board
/Balance3/CELL_SENSE: C19.2, C20.1, Q8.3 (D), R49.1; also elsewhere on the board
/Balance3/V_BELOW: R47.2, R48.2, R53.2; also elsewhere on the board
/Balance4/CELL_SENSE: C18.2, C19.1, Q7.3 (D), R45.1; also elsewhere on the board
/Balance4/V_BELOW: R43.2, R44.2, R49.2; also elsewhere on the board
/Balance5/CELL_SENSE: C17.2, C18.1, Q6.3 (D), R41.1; also elsewhere on the board
/Balance5/V_BELOW: R39.2, R40.2, R45.2; also elsewhere on the board
/Balance6/CELL_SENSE: C16.2, C17.1, Q5.3 (D), R37.1; also elsewhere on the board
/Balance6/V_BELOW: R35.2, R36.2, R41.2; also elsewhere on the board
/Balance7/CELL_SENSE: C15.2, C16.1, Q4.3 (D), R33.1; also elsewhere on the board
/Balance8/CELL_SENSE: C15.1, Q3.3 (D), R29.1; also elsewhere on the board
/Balance8/V_BELOW: R27.2, R28.2, R33.2; also elsewhere on the board
/Balance9/CELL_SENSE: C23.2; also elsewhere on the board
/Balance10/CELL_SENSE: C23.1, Q11.3 (D), R61.1; also elsewhere on the board
/Balance10/V_BELOW: R59.2, R60.2; also elsewhere on the board
/Balance10/V_CELL: R61.2; also elsewhere on the board
/Control1: R58.1; also elsewhere on the board
/Control2: R54.1; also elsewhere on the board
/Control3: C20.2; also elsewhere on the board
/Control4: R46.1; also elsewhere on the board
/Control5: R42.1; also elsewhere on the board
/Control6: R38.1; also elsewhere on the board
/Control7: R34.1; also elsewhere on the board
/Control8: R30.1; also elsewhere on the board
/Control10: R62.1; also elsewhere on the board
GND: R55.2, R56.2; also elsewhere on the board
unnamed: D3.1 (K), R27.1
unnamed: D3.2 (A), Q3.2 (S), R28.3
unnamed: D4.1 (K), R31.1
unnamed: D5.1 (K), R35.1
unnamed: D5.2 (A), Q5.2 (S), R36.3
unnamed: D6.1 (K), R39.1
unnamed: D6.2 (A), Q6.2 (S), R40.3
unnamed: D7.1 (K), R43.1
unnamed: D7.2 (A), Q7.2 (S), R44.3
unnamed: D8.1 (K), R47.1
unnamed: D8.2 (A), Q8.2 (S), R48.3
unnamed: D9.1 (K), R51.1
unnamed: D9.2 (A), Q9.2 (S), R52.3
unnamed: D10.1 (K), R55.1
unnamed: D10.2 (A), Q10.2 (S), R56.3
unnamed: D11.1 (K), R59.1
unnamed: D11.2 (A), Q11.2 (S), R60.3
unnamed: Q3.1 (G), R30.2
unnamed: Q4.1 (G), R34.2
unnamed: Q5.1 (G), R38.2
unnamed: Q6.1 (G), R42.2
unnamed: Q7.1 (G), R46.2
unnamed: Q8.1 (G), R50.2
unnamed: Q9.1 (G), R54.2
unnamed: Q10.1 (G), R58.2
unnamed: Q11.1 (G), R62.2

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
